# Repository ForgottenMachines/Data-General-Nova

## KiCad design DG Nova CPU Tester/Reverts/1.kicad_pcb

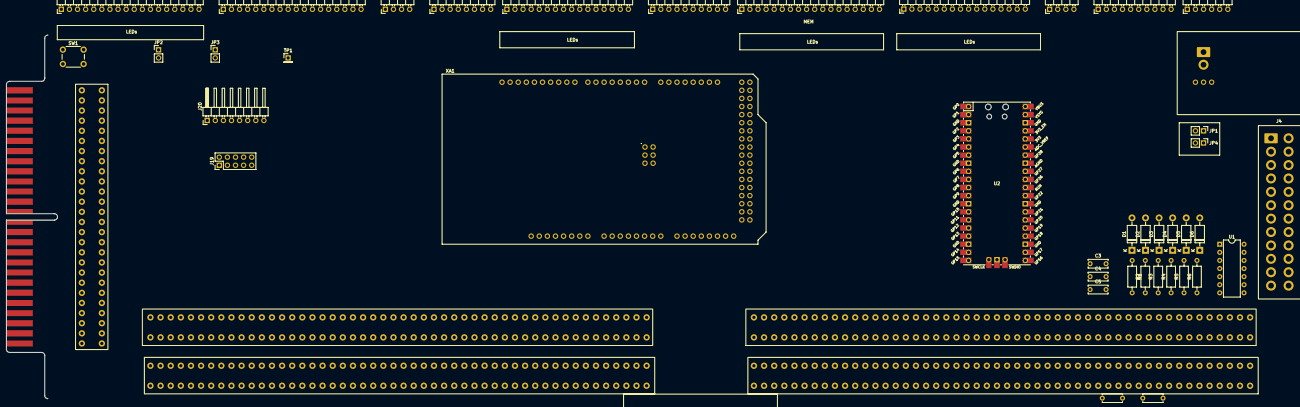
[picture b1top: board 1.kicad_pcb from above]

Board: 2 copper layers, 48 parts (0 on the bottom side), 153 nets, no tracks yet.

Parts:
C1, C2: CAP_Disc_Common_-_Entrex_Trapezoid; Disc Capacitor Common Entrex Trapezoid
C3, C4, C5: C; C_Disc_D6.0mm_W2.5mm_P5.00mm
D1, D2, D3, D4, D5, D6: 1N4004; D_DO-41_SOD81_P10.16mm_Horizontal
FPIMAGE1: MountingHole; nova frontpanel layout
J1: Front Panel Socket - Backside; DG NOVA Front Pannel Connector - Backside
J2, J3: DG NOVA Backplane Connector - Frontside
J4: ATX-24; Connector_2x12_P4.2mmx5.5mm (ATX Plug)
J5: Front Panel Card Edge; DG Nova Front Panel Card Edge
J6: MBO; PinHeader_1x16_P2.54mm_Horizontal
J7: MEM; PinHeader_1x18_P2.54mm_Horizontal
J8: Data Channel; PinHeader_1x16_P2.54mm_Horizontal
J9: Front Panel Controls; PinHeader_1x18_P2.54mm_Horizontal
J10: Programmed I/O; PinHeader_1x18_P2.54mm_Horizontal
J11: CPU Option Inputs; PinHeader_1x10_P2.54mm_Horizontal
J12: Data Channel; PinHeader_1x08_P2.54mm_Horizontal
J13: Program Interrupt; PinHeader_1x04_P2.54mm_Horizontal
J14: System Control; PinHeader_1x04_P2.54mm_Horizontal
J15, J16: Slot_02x50_Odd_Even; DG NOVA Backplane Connector - Backside
J17: CPU Option Outputs; PinHeader_1x06_P2.54mm_Horizontal
J18: MEM Control Outputs; PinHeader_1x10_P2.54mm_Horizontal
J19: Logic 8 CH; PinHeader_2x05_P2.54mm_Vertical
J20: Logic 8 CH; PinHeader_1x08_P2.54mm_Horizontal
JP1, JP4: Vipass Ammeter; PinHeader_1x02_P2.54mm_Vertical
JP2: Entrex ~{M CON DATA}; PinHeader_1x02_P2.54mm_Vertical
JP3: Entrex ~{M CON INST}; PinHeader_1x02_P2.54mm_Vertical
MES1: XK-001; XK-001_Volt-Amp_Meter - Backside
R1, R6: 1k; R_Axial_DIN0207_L6.3mm_D2.5mm_P10.16mm_Horizontal
R2, R5: 10k; R_Axial_DIN0207_L6.3mm_D2.5mm_P10.16mm_Horizontal
R3, R4: 4.7k; R_Axial_DIN0207_L6.3mm_D2.5mm_P10.16mm_Horizontal
SW1: SW_Push; SW_PUSH_6mm
TP1: Entrex Backplane S01B53 to S13B53; PinHeader_1x01_P2.54mm_Vertical
U1: 74HC14; DIP-14_W7.62mm
U2: Pico; RPi_Pico_SMD_TH
XA1: Arduino_Mega2560_Shield

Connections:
+3v3: J4.1 (+3.3V), J4.2 (+3.3V), J4.12 (+3.3V), J4.13 (+3.3V)
+5V: D1.1 (K), D2.2 (A), D3.1 (K), D4.2 (A), D5.1 (K), D6.2 (A), J2.3, J2.4, J2.97, J2.98, J3.3, J3.4, J3.97, J3.98, J4.4 (+5V), J4.6 (+5V), J4.21 (+5V), J4.22 (+5V), J4.23 (+5V), J5.27, J15.3, J15.4, J15.97 (Pin_69), J15.98, J16.3, J16.4, J16.97 (Pin_69), J16.98, MES1.1, MES1.3 (PWR), U1.14 (VCC), U2.39 (VSYS), XA1.5V1 (5V), XA1.5V3 (5V), XA1.5V4 (5V), XA1.VIN
+5V OK: J2.8, J14.3, U1.12
+12V Lamp: J1.33, J4.10 (+12V), J4.11 (+12V), J5.33
+VINH: J15.10, J16.84
-5V: J15.6, J16.81
CLK FLOP: J3.48, J17.1
CLR: J2.50, J10.14, J15.50
DATIA: J2.44, J10.7, J15.44
DATIB: J2.42, J10.8, J15.42
DATIC: J2.54, J10.9, J15.54
DATOA: J2.58, J10.10, J15.58
DATOB: J2.56, J10.11, J15.56
DATOC: J2.48, J10.12, J15.48
DCHI: J3.37, J12.6, J16.37
DCHO: J3.33, J12.7, J16.33
Entrex Backplane S01B53 to S13B53: J3.53, TP1.1
Entrex P10.19: J2.24, JP3.2 (B)
Entrex P10.30: J2.29, JP2.2 (B)
GND: C1.1, C2.1, C3.2, C4.2, C5.2, J1.1, J1.40, J2.1, J2.2, J2.33, J2.34, J2.99, J2.100, J3.1, J3.2, J3.50, J3.99, J3.100, J5.1, J5.40, J15.1, J15.2, J15.33, J15.34, J15.99, J15.100, J16.1, J16.2, J16.50, J16.89, J16.92, J16.99, J16.100, J19.10, JP1.2 (B), JP4.2 (B), MES1.5, SW1.1, U1.7 (GND), U2.3 (GND), U2.8 (GND), U2.13 (GND), U2.18 (GND), U2.23 (GND), U2.28 (GND), U2.33 (AGND), U2.38 (GND), U2.42 (GND), XA1.GND1 (GND), XA1.GND2 (GND), XA1.GND3 (GND), XA1.GND5 (GND), XA1.GND6 (GND)
GND After Meter: J4.3 (GND), J4.5 (GND), J4.7 (GND), J4.15 (GND), J4.17 (GND), J4.18 (GND), J4.19 (GND), J4.24 (GND), JP1.1 (A), JP4.1 (A), MES1.2, MES1.4
INH GND: J15.8, J15.14, J15.16, J15.20, J15.22, J15.26, J15.30, J15.31
INHIBIT: J3.30, J16.30, J18.9
INTA: J2.40, J13.4, J15.40
IO PLS: J2.74, J10.15, J15.74
IO RST: J2.70, J14.1, J15.70
LOAD IR: J2.73, J17.3
Logic1: J19.1, J20.1
Logic2: J19.2, J20.2
Logic3: J19.3, J20.3
Logic4: J19.4, J20.4
Logic5: J19.5, J20.5
Logic6: J19.6, J20.6
Logic7: J19.7, J20.7
Logic8: J19.8, J20.8
MB LOAD: J3.74, J16.74, J18.6
MEM OK: J2.9, J7.18, U1.10, XA1.D52
unnamed: C3.1, R1.2, R2.1, U1.5
unnamed: C4.1, R3.2, R4.1, U1.3
unnamed: C5.1, R5.2, R6.1, U1.1
unnamed: D1.2 (A), R1.1
unnamed: D2.1 (K), R2.2
unnamed: D3.2 (A), R3.1
unnamed: D4.1 (K), R4.2
unnamed: D5.2 (A), R5.1
unnamed: D6.1 (K), R6.2
unnamed: U1.6, U1.9
unnamed: U1.4, U1.11
unnamed: U1.2, U1.13
unnamed: SW1.2, XA1.RST1 (RESET)
OVFLO: J3.39, J12.8, J16.39
RESTART ENABLE: J1.19, J2.32, J5.19, J9.16, XA1.A7
STROBE: J3.20, J16.20, J18.8
STRT: J2.52, J10.13, J15.52
~CARRY: J1.49, J2.15, J5.49, J9.3, XA1.D32
~CON DATA: J1.46, J2.28, J5.46, J9.11, JP2.1 (A), XA1.D0 (D0_RX0)
~CON INST: J1.22, J2.22, J5.22, J9.10, JP3.1 (A), XA1.A4
~CON RQ: C2.2, J1.21, J2.27, J5.21, J9.9, XA1.A5
~CONT+ISTP+MSTP: J1.47, J2.25, J5.47, J9.12, XA1.D1 (D1_TX0)
~DATA0: J3.62, J8.1, J16.62
~DATA1: J3.65, J8.2, J16.65
~DATA2: J3.82, J8.3, J16.82
~DATA3: J3.73, J8.4, J16.73
~DATA4: J3.61, J8.5, J16.61
~DATA5: J3.57, J8.6, J16.57
~DATA6: J3.95, J8.7, J16.95
~DATA7: J3.55, J8.8, J16.55
~DATA8: J3.60, J8.9, J16.60
~DATA9: J3.63, J8.10, J16.63
~DATA10: J3.75, J8.11, J16.75
~DATA11: J3.58, J8.12, J16.58
~DATA12: J3.59, J8.13, J16.59
~DATA13: J3.64, J8.14, J16.64
~DATA14: J3.56, J8.15, J16.56
~DATA15: J3.66, J8.16, J16.66
~DCHA: J2.60, J12.3, J15.60
~DCHM0: J3.17, J12.4, J16.17
~DCHM1: J3.21, J12.5, J16.21
~DCHR: J3.35, J12.1, J16.35
~DEFER: J1.52, J2.12, J5.52, J9.5, XA1.D50
~DIV: J2.91, J11.2
~DRIVE IO: J3.88, J16.88, J18.1
~DS0: J2.72, J10.1, J15.72
~DS1: J2.68, J10.2, J15.68
~DS2: J2.66, J10.3, J15.66
~DS3: J2.46, J10.4, J15.46
~DS4: J2.62, J10.5, J15.62
~DS5: J2.64, J10.6, J15.64
~EXEC: J1.51, J2.11, J5.51, J9.6, XA1.D51
~EXT LOAD: J2.47, J3.49, J11.4
~FETCH: J1.50, J2.13, J2.49, J5.50, J9.4, XA1.D49
~FORCE LOAD IR: J2.85, J11.3
~INH TRANS: J3.45, J16.45, J18.10
~INTR: J3.29, J13.1, J16.29
~ION: J1.25, J2.16, J5.25, J9.2, XA1.D31
~ISTP: J1.24, J2.17, J5.24, J9.14, XA1.A2
~LOAD AC: J2.77, J17.2
~MA LOAD: J3.7, J16.7, J18.5
~MB CLEAR: J3.86, J16.86, J18.7
~MBO0: J3.79, J6.1, J16.79
~MBO1: J1.14, J3.77, J5.14, J6.2, J16.77, XA1.D15 (D15_RX3)
~MBO2: J1.15, J3.44, J5.15, J6.3, J16.44, XA1.D16 (D16_TX2)
~MBO3: J1.38, J3.43, J5.38, J6.4, J16.43, XA1.D17 (D17_RX2)
~MBO4: J1.16, J3.42, J5.16, J6.5, J16.42, XA1.D18 (D18_TX1)
~MBO5: J1.11, J3.32, J5.11, J6.6, J16.32, XA1.D19 (D19_RX1)
~MBO6: J1.35, J3.16, J5.35, J6.7, J16.16, XA1.D20 (D20_SDA)
~MBO7: J1.9, J3.14, J5.9, J6.8, J16.14, XA1.D21 (D21_SCL)
~MBO8: J1.18, J3.12, J5.18, J6.9, J16.12, XA1.D22
~MBO9: J1.8, J3.9, J5.8, J6.10, J16.9, XA1.D23
~MBO10: J1.44, J3.8, J5.44, J6.11, J16.8, XA1.D24
~MBO11: J1.6, J3.5, J5.6, J6.12, J16.5, XA1.D25
~MBO12: J1.30, J2.39, J5.30, J6.13, J15.39, XA1.D26
~MBO13: J1.4, J2.37, J5.4, J6.14, J15.37, XA1.D27
~MBO14: J1.12, J2.43, J5.12, J6.15, J15.43, XA1.D28
~MBO15: J1.28, J2.41, J5.28, J6.16, J15.41, XA1.D29
~MD SEL1: J2.87, J17.4
~MEM0: J1.39, J3.71, J5.39, J7.1, J16.71, XA1.D33
~MEM1: J1.41, J3.70, J5.41, J7.2, J16.70, XA1.D34
~MEM2: J1.13, J3.47, J5.13, J7.3, J16.47, XA1.D35
~MEM3: J1.43, J3.68, J5.43, J7.4, J16.68, XA1.D36
~MEM4: J1.37, J3.28, J5.37, J7.5, J16.28, XA1.D37
~MEM5: J1.36, J3.26, J5.36, J7.6, J16.26, XA1.D38
~MEM6: J1.10, J3.22, J5.10, J7.7, J16.22, XA1.D39
~MEM7: J1.42, J3.24, J5.42, J7.8, J16.24, XA1.D40
~MEM8: J1.34, J2.55, J5.34, J7.9, J15.55, XA1.D41
~MEM9: J1.7, J2.53, J5.7, J7.10, J15.53, XA1.D42
~MEM10: J1.32, J2.45, J5.32, J7.11, J15.45, XA1.D43
~MEM11: J1.31, J2.51, J5.31, J7.12, J15.51, XA1.D44
~MEM12: J1.5, J2.36, J5.5, J7.13, J15.36, XA1.D45
~MEM13: J1.29, J2.35, J5.29, J7.14, J15.35, XA1.D46
~MEM14: J1.3, J3.76, J5.3, J7.15, J16.76, XA1.D47
~MEM15: J1.2, J3.18, J5.2, J7.16, J16.18, XA1.D48
~MSKO: J2.38, J13.2, J15.38
~MSTP: J1.48, J2.20, J5.48, J9.13
~PL: C1.2, J1.23, J2.19, J5.23, J9.15, XA1.A3
~POWER FAIL: J2.5, J14.4, U1.8
~READ1: J3.87, J16.87, J18.3
~READ2: J3.90, J16.90, J18.4
~READ IO: J3.83, J16.83, J18.2
~RQENB: J3.41, J14.2, J16.41
~RST: J1.20, J2.30, J5.20, J9.17, XA1.A6
~RUN: J1.26, J2.14, J5.26, J9.1, XA1.D30
~SELB: J2.82, J10.16, J15.82
~SELD: J2.80, J10.17, J15.80
~SHIFT0: J3.94, J11.7
~SHIFT1: J3.96, J11.8
~SHIFT2: J3.93, J11.9
~SHIFT3: J3.91, J11.10
~SKIP: J3.69, J9.7
~STOP: J1.45, J2.31, J5.45, J9.8, XA1.D14 (D14_TX3)
~TEST: J2.92, J11.5
~WAS JSR: J2.89, J17.5
~WHOA: J3.6, J11.1

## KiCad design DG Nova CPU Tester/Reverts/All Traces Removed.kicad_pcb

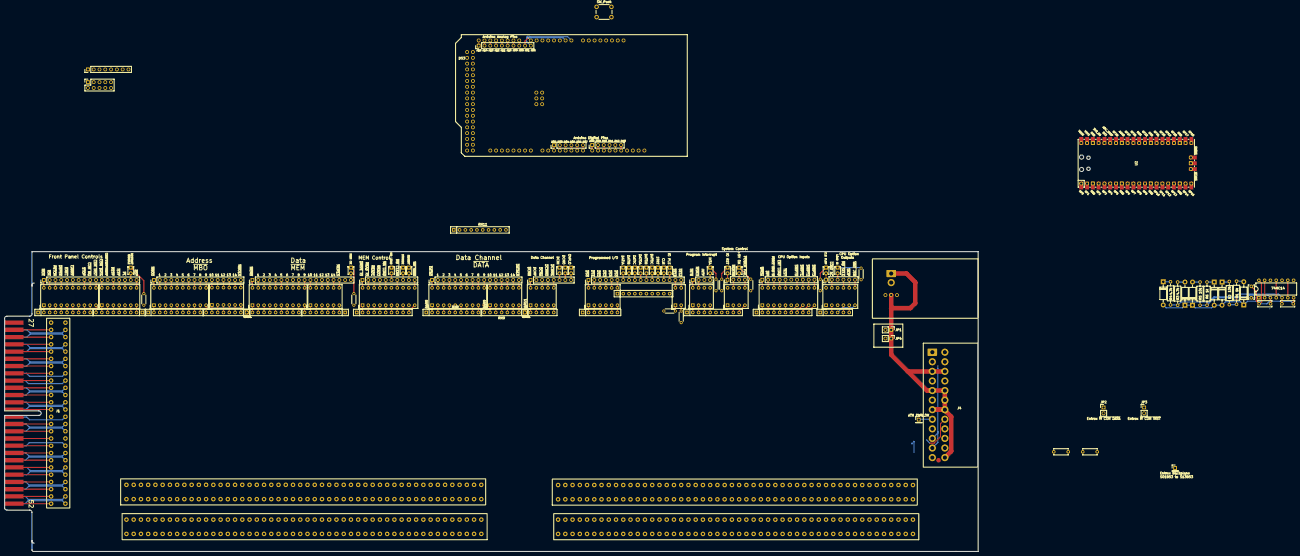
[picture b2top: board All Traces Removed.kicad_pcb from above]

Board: 2 copper layers, 426.8 x 131.4 mm, 115 parts (0 on the bottom side), 304 nets.

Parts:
BAR1, BAR3, BAR5, BAR7, BAR8, BAR15: LED Bar 10
BAR2: LED Bar 10; LED Bar 7
BAR4, BAR6, BAR9, BAR10, BAR16: LED Bar 10; LED Bar 6
BAR11: LED Bar 10; LED Bar 5
BAR12: LED Bar 2
BAR13, BAR14: LED Bar 4
C1, C2: CAP_Disc_Common_-_Entrex_Trapezoid; Disc Capacitor Common Entrex Trapezoid
C3, C4, C5: C; C_Disc_D6.0mm_W2.5mm_P5.00mm
D1, D2, D3, D4, D5, D6: 1N4004; D_DO-41_SOD81_P10.16mm_Horizontal
D7, D8, D9, D10, D11, D12, D13, D14, D15, D16, D17, D18, D19, D20, D21, D22, D23, D24, D25, D26, D27, D28: LED; LED_D1.8mm_W3.3mm_H2.4mm
FPIMAGE1: MountingHole; nova frontpanel layout
J1: Front Panel Socket - Backside; DG NOVA Front Pannel Connector - Backside
J2, J3: DG NOVA Backplane Connector - Frontside
J4: ATX-24; Connector_2x12_P4.2mmx5.5mm (ATX Plug)
J5: Front Panel Card Edge; DG Nova Front Panel Card Edge
J6: MBO; PinHeader_1x16_P2.54mm_Vertical
J7: MEM; PinHeader_1x18_P2.54mm_Vertical
J8: Data Channel; PinHeader_1x16_P2.54mm_Vertical
J9: Front Panel Controls; PinHeader_1x17_P2.54mm_Vertical
J10: Programmed I/O; PinHeader_1x17_P2.54mm_Vertical
J11: CPU Option Inputs; PinHeader_1x10_P2.54mm_Vertical
J12: Data Channel; PinHeader_1x08_P2.54mm_Vertical
J13: Program Interrupt; PinHeader_1x04_P2.54mm_Vertical
J14: System Control; PinHeader_1x04_P2.54mm_Vertical
J15, J16: Slot_02x50_Odd_Even; DG NOVA Backplane Connector - Backside
J17: CPU Option Outputs; PinHeader_1x06_P2.54mm_Vertical
J18: MEM Control Outputs; PinHeader_1x10_P2.54mm_Vertical
J19: Logic 8 CH; PinHeader_2x05_P2.54mm_Vertical - Backside
J20: Logic 8 CH; PinHeader_1x08_P2.54mm_Vertical
J21: Arduino Anolog Pins; PinHeader_1x10_P2.54mm_Vertical
J22, J23: Arduino Digital Pins; PinHeader_1x06_P2.54mm_Vertical
JP1, JP4: Vipass Ammeter; PinHeader_1x02_P2.54mm_Vertical
JP2: Entrex ~{M CON DATA}; PinHeader_1x02_P2.54mm_Vertical
JP3: Entrex ~{M CON INST}; PinHeader_1x02_P2.54mm_Vertical
MES1: XK-001; XK-001_Volt-Amp_Meter - Backside
R1, R6: 1k; R_Axial_DIN0207_L6.3mm_D2.5mm_P10.16mm_Horizontal
R2, R5: 10k; R_Axial_DIN0207_L6.3mm_D2.5mm_P10.16mm_Horizontal
R3, R4: 4.7k; R_Axial_DIN0207_L6.3mm_D2.5mm_P10.16mm_Horizontal
R7, R8, R9, R10, R11, R12, R13, R14, R15: R_US; R_Axial_DIN0204_L3.6mm_D1.6mm_P5.08mm_Horizontal
RN1, RN3, RN5, RN7, RN8, RN11, RN13, RN14, RN15: R_Network09_US; R_Array_SIP10
RN2: R_Network08_US; R_Array_SIP9
RN4, RN6, RN9: R_Network07_US; R_Array_SIP8
RN10, RN16: R_Network05_US; R_Array_SIP6
RN12: R_Network06_US; R_Array_SIP7
SW1: SW_Push; SW_PUSH_6mm
TP1: Entrex Backplane S01B53 to S13B53; PinHeader_1x01_P2.54mm_Vertical
TP2: ATX PWR_OK; PinHeader_1x01_P2.54mm_Vertical
U1: 74HC14; DIP-14_W7.62mm
U2: Pico; RPi_Pico_SMD_TH
XA1: Arduino_Mega2560_Shield

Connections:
+3v3: J4.1 (+3.3V), J4.2 (+3.3V), J4.12 (+3.3V), J4.13 (+3.3V)
+5V: D1.1 (K), D2.2 (A), D3.1 (K), D4.2 (A), D5.1 (K), D6.2 (A), J1.27, J2.3, J2.4, J2.97, J2.98, J3.3, J3.4, J3.97, J3.98, J4.4 (+5V), J4.6 (+5V), J4.21 (+5V), J4.22 (+5V), J4.23 (+5V), J5.27, J15.3, J15.4, J15.97 (Pin_69), J15.98, J16.3, J16.4, J16.97 (Pin_69), J16.98, MES1.1, MES1.3 (PWR), R9.1, R10.1, RN1.1 (common), RN2.1 (common), RN3.1 (common), RN4.1 (common), RN5.1 (common), RN6.1 (common), RN7.1 (common), RN8.1 (common), RN9.1 (common), RN10.1 (common), RN12.1 (common), RN13.1 (common), RN15.1 (common), RN16.1 (common), U1.14 (VCC), U2.39 (VSYS), XA1.5V1 (5V), XA1.5V3 (5V), XA1.5V4 (5V), XA1.VIN
+5V OK: D24.2 (A), J2.8, J14.3, U1.12
+12V Lamp: J1.33, J4.10 (+12V), J4.11 (+12V), J5.33
+VINH: J15.10, J16.84
-5V: J4.20 (-5v), J15.6, J16.81
CLK FLOP: D28.2 (A), J3.48, J17.1
CLR: D20.2 (A), J2.50, J10.14, J15.50
DATIA: D12.2 (A), J2.44, J10.7, J15.44
DATIB: D16.2 (A), J2.42, J10.8, J15.42
DATIC: D17.2 (A), J2.54, J10.9, J15.54
DATOA: D21.2 (A), J2.58, J10.10, J15.58
DATOB: D22.2 (A), J2.56, J10.11, J15.56
DATOC: D18.2 (A), J2.48, J10.12, J15.48
DCHI: D13.2 (A), J3.37, J12.6, J16.37
DCHO: D14.2 (A), J3.33, J12.7, J16.33
Entrex Backplane S01B53 to S13B53: J3.53, TP1.1
Entrex P10.19: J2.24, JP3.2 (B)
Entrex P10.30: J2.29, JP2.2 (B)
GND: C1.1, C2.1, C3.2, C4.2, C5.2, J1.1, J1.40, J2.1, J2.2, J2.33, J2.34, J2.99, J2.100, J3.1, J3.2, J3.50, J3.99, J3.100, J5.1, J5.40, J15.1, J15.2, J15.33, J15.34, J15.99, J15.100, J16.1, J16.2, J16.50, J16.89, J16.92, J16.99, J16.100, J19.10, JP1.2 (B), JP4.2 (B), MES1.5, R7.1, R8.1, R11.1, R12.1, R13.1, R14.1, R15.1, RN11.1 (common), RN14.1 (common), SW1.1, U1.7 (GND), U2.3 (GND), U2.8 (GND), U2.13 (GND), U2.18 (GND), U2.23 (GND), U2.28 (GND), U2.33 (AGND), U2.38 (GND), U2.42 (GND), XA1.GND1 (GND), XA1.GND2 (GND), XA1.GND3 (GND), XA1.GND5 (GND), XA1.GND6 (GND)
GND After Meter: J4.3 (GND), J4.5 (GND), J4.7 (GND), J4.15 (GND), J4.17 (GND), J4.18 (GND), J4.19 (GND), J4.24 (GND), JP1.1 (A), JP4.1 (A), MES1.2, MES1.4
INH GND: J15.8, J15.14, J15.16, J15.20, J15.22, J15.26, J15.30, J15.31
INHIBIT: D11.2 (A), J3.30, J16.30, J18.9
INTA: D25.2 (A), J2.40, J13.4, J15.40
IO PLS: D23.2 (A), J2.74, J10.15, J15.74
IO RST: D26.2 (A), J2.70, J14.1, J15.70
LOAD IR: D27.2 (A), J2.73, J17.3
Logic1: J19.1, J20.1
Logic2: J19.2, J20.2
Logic3: J19.3, J20.3
Logic4: J19.4, J20.4
Logic5: J19.5, J20.5
Logic6: J19.6, J20.6
Logic7: J19.7, J20.7
Logic8: J19.8, J20.8
MB LOAD: D9.2 (A), J3.74, J16.74, J18.6
MEM OK: D8.2 (A), J2.9, J7.18, U1.10, XA1.D52
unnamed: BAR12.1, R10.2
unnamed: BAR12.2, R9.2
unnamed: C3.1, R1.2, R2.1, U1.5
unnamed: C4.1, R3.2, R4.1, U1.3
unnamed: C5.1, R5.2, R6.1, U1.1
unnamed: D1.2 (A), R1.1
unnamed: D2.1 (K), R2.2
unnamed: D3.2 (A), R3.1
unnamed: D4.1 (K), R4.2
unnamed: D5.2 (A), R5.1
unnamed: D6.1 (K), R6.2
unnamed: D7.1 (K), R7.2
unnamed: D8.1 (K), R8.2
unnamed: D9.1 (K), RN11.2 (R1)
unnamed: D10.1 (K), RN11.3 (R2)
unnamed: D11.1 (K), RN11.4 (R3)
unnamed: D12.1 (K), RN14.2 (R1)
unnamed: D13.1 (K), RN11.7 (R6)
unnamed: D14.1 (K), RN11.8 (R7)
unnamed: D15.1 (K), RN11.9 (R8)
unnamed: D16.1 (K), RN14.3 (R2)
unnamed: D17.1 (K), RN14.4 (R3)
unnamed: D18.1 (K), RN14.7 (R6)
unnamed: D19.1 (K), RN14.8 (R7)
unnamed: D20.1 (K), RN14.9 (R8)
unnamed: D21.1 (K), RN14.5 (R4)
unnamed: D22.1 (K), RN14.6 (R5)
unnamed: D23.1 (K), RN14.10 (R9)
unnamed: D24.1 (K), R14.2
unnamed: D25.1 (K), R11.2
unnamed: D26.1 (K), R12.2
unnamed: D27.1 (K), R13.2
unnamed: D28.1 (K), R15.2
unnamed: J21.1, XA1.A15
unnamed: J21.2, XA1.A14
unnamed: J21.3, XA1.A13
unnamed: J21.4, XA1.A12
unnamed: J21.5, XA1.A11
unnamed: J21.6, XA1.A10
unnamed: J21.7, XA1.A9
unnamed: J21.8, XA1.A8
unnamed: J21.9, XA1.A1
unnamed: J21.10, XA1.A0
unnamed: J22.1, XA1.D2 (D2_INT0)
unnamed: J22.2, XA1.D3 (D3_INT1)
unnamed: J22.3, XA1.D4
unnamed: J22.4, XA1.D5
unnamed: J22.5, XA1.D6
unnamed: J22.6, XA1.D7
unnamed: J23.1, XA1.D8
unnamed: J23.2, XA1.D9
unnamed: J23.3, XA1.D10
unnamed: J23.4, XA1.D11
unnamed: J23.5, XA1.D12
unnamed: J23.6, XA1.D13
unnamed: BAR1.1, RN1.2 (R1)
unnamed: BAR1.2, RN1.3 (R2)
unnamed: BAR1.3, RN1.4 (R3)
unnamed: BAR1.4, RN1.5 (R4)
unnamed: BAR1.5, RN1.6 (R5)
unnamed: BAR1.6, RN1.7 (R6)
unnamed: BAR1.7, RN1.8 (R7)
unnamed: BAR1.8, RN1.9 (R8)
unnamed: BAR1.9, RN1.10 (R9)
unnamed: BAR2.7, RN2.2 (R1)
unnamed: BAR2.6, RN2.3 (R2)
unnamed: BAR2.5, RN2.4 (R3)
unnamed: BAR2.4, RN2.5 (R4)
unnamed: BAR2.3, RN2.6 (R5)
unnamed: BAR2.2, RN2.7 (R6)
unnamed: BAR2.1, RN2.8 (R7)
unnamed: BAR1.10, RN2.9 (R8)
unnamed: BAR3.1, RN3.2 (R1)
unnamed: BAR3.2, RN3.3 (R2)
unnamed: BAR3.3, RN3.4 (R3)
unnamed: BAR3.4, RN3.5 (R4)
unnamed: BAR3.5, RN3.6 (R5)
unnamed: BAR3.6, RN3.7 (R6)
unnamed: BAR3.7, RN3.8 (R7)
unnamed: BAR3.8, RN3.9 (R8)
unnamed: BAR3.9, RN3.10 (R9)
unnamed: BAR4.6, RN4.2 (R1)
unnamed: BAR4.5, RN4.3 (R2)
unnamed: BAR4.4, RN4.4 (R3)
unnamed: BAR4.3, RN4.5 (R4)
unnamed: BAR4.2, RN4.6 (R5)
unnamed: BAR4.1, RN4.7 (R6)
unnamed: BAR3.10, RN4.8 (R7)
unnamed: BAR5.1, RN5.2 (R1)
unnamed: BAR5.2, RN5.3 (R2)
unnamed: BAR5.3, RN5.4 (R3)
unnamed: BAR5.4, RN5.5 (R4)
unnamed: BAR5.5, RN5.6 (R5)
unnamed: BAR5.6, RN5.7 (R6)
unnamed: BAR5.7, RN5.8 (R7)
unnamed: BAR5.8, RN5.9 (R8)
unnamed: BAR5.9, RN5.10 (R9)
unnamed: BAR6.6, RN6.2 (R1)
unnamed: BAR6.5, RN6.3 (R2)
unnamed: BAR6.4, RN6.4 (R3)
unnamed: BAR6.3, RN6.5 (R4)
unnamed: BAR6.2, RN6.6 (R5)
unnamed: BAR6.1, RN6.7 (R6)
unnamed: BAR5.10, RN6.8 (R7)
unnamed: BAR7.1, RN7.2 (R1)
unnamed: BAR7.2, RN7.3 (R2)
unnamed: BAR7.3, RN7.4 (R3)
unnamed: BAR7.4, RN7.5 (R4)
unnamed: BAR7.5, RN7.6 (R5)
unnamed: BAR7.6, RN7.7 (R6)
unnamed: BAR7.7, RN7.8 (R7)
unnamed: BAR7.8, RN7.9 (R8)
unnamed: BAR7.10, RN7.10 (R9)
unnamed: BAR8.1, RN8.2 (R1)
unnamed: BAR8.2, RN8.3 (R2)
unnamed: BAR8.3, RN8.4 (R3)
unnamed: BAR8.4, RN8.5 (R4)
unnamed: BAR8.5, RN8.6 (R5)
unnamed: BAR8.6, RN8.7 (R6)
unnamed: BAR8.7, RN8.8 (R7)
unnamed: BAR8.8, RN8.9 (R8)
unnamed: BAR8.9, RN8.10 (R9)
unnamed: BAR9.6, RN9.2 (R1)
unnamed: BAR9.5, RN9.3 (R2)
unnamed: BAR9.4, RN9.4 (R3)
unnamed: BAR9.3, RN9.5 (R4)
unnamed: BAR9.2, RN9.6 (R5)
unnamed: BAR9.1, RN9.7 (R6)
unnamed: BAR8.10, RN9.8 (R7)
unnamed: BAR11.1, RN10.2 (R1)
unnamed: BAR11.2, RN10.3 (R2)
unnamed: BAR11.3, RN10.4 (R3)
unnamed: BAR11.4, RN10.5 (R4)
unnamed: BAR11.5, RN10.6 (R5)
unnamed: BAR10.1, RN12.2 (R1)
unnamed: BAR10.2, RN12.3 (R2)
unnamed: BAR10.3, RN12.4 (R3)
unnamed: BAR10.4, RN12.5 (R4)
unnamed: BAR10.5, RN12.6 (R5)
unnamed: BAR10.6, RN12.7 (R6)
unnamed: BAR13.1, RN13.2 (R1)
unnamed: BAR13.2, RN13.3 (R2)
unnamed: BAR13.3, RN13.4 (R3)
unnamed: BAR13.4, RN13.5 (R4)
unnamed: BAR14.2, RN13.9 (R8)
unnamed: BAR14.4, RN13.10 (R9)
unnamed: BAR15.1, RN15.2 (R1)
unnamed: BAR15.2, RN15.3 (R2)
unnamed: BAR15.3, RN15.4 (R3)
unnamed: BAR15.4, RN15.5 (R4)
unnamed: BAR15.5, RN15.6 (R5)
unnamed: BAR15.7, RN15.7 (R6)
unnamed: BAR15.8, RN15.8 (R7)
unnamed: BAR15.9, RN15.9 (R8)
unnamed: BAR15.10, RN15.10 (R9)
unnamed: BAR16.2, RN16.3 (R2)
unnamed: BAR16.6, RN16.4 (R3)
unnamed: BAR16.4, RN16.5 (R4)
unnamed: BAR16.5, RN16.6 (R5)
unnamed: U1.6, U1.9
unnamed: U1.4, U1.11
unnamed: U1.2, U1.13
unnamed: SW1.2, XA1.RST1 (RESET)
OVFLO: D15.2 (A), J3.39, J12.8, J16.39
PWR_OK: J4.8 (PWR_OK), TP2.1
RESTART ENABLE: D7.2 (A), J1.19, J2.32, J5.19, J9.16, XA1.A7
STROBE: D10.2 (A), J3.20, J16.20, J18.8
STRT: D19.2 (A), J2.52, J10.13, J15.52
~CARRY: BAR1.15 (K), J1.49, J2.15, J5.49, J9.6, XA1.D32
~CON DATA: BAR2.20 (K), J1.46, J2.28, J5.46, J9.11, JP2.1 (A), XA1.D0 (D0_RX0)
~CON INST: BAR1.11 (K), J1.22, J2.22, J5.22, J9.10, JP3.1 (A), XA1.A4
~CON RQ: BAR1.12 (K), C2.2, J1.21, J2.27, J5.21, J9.9, XA1.A5
~CONT+ISTP+MSTP: BAR2.19 (K), J1.47, J2.25, J5.47, J9.12, XA1.D1 (D1_TX0)
~DATA0: BAR8.20 (K), J3.62, J8.1, J16.62
~DATA1: BAR8.19 (K), J3.65, J8.2, J16.65
~DATA2: BAR8.18 (K), J3.82, J8.3, J16.82
~DATA3: BAR8.17 (K), J3.73, J8.4, J16.73
~DATA4: BAR8.16 (K), J3.61, J8.5, J16.61
~DATA5: BAR8.15 (K), J3.57, J8.6, J16.57
~DATA6: BAR8.14 (K), J3.95, J8.7, J16.95
~DATA7: BAR8.13 (K), J3.55, J8.8, J16.55
~DATA8: BAR8.12 (K), J3.60, J8.9, J16.60
~DATA9: BAR8.11 (K), J3.63, J8.10, J16.63
~DATA10: BAR9.20 (K), J3.75, J8.11, J16.75
~DATA11: BAR9.19 (K), J3.58, J8.12, J16.58
~DATA12: BAR9.18 (K), J3.59, J8.13, J16.59
~DATA13: BAR9.17 (K), J3.64, J8.14, J16.64
~DATA14: BAR9.16 (K), J3.56, J8.15, J16.56
~DATA15: BAR9.15 (K), J3.66, J8.16, J16.66
~DCHA: BAR11.18 (K), J2.60, J12.3, J15.60
~DCHM0: BAR11.17 (K), J3.17, J12.4, J16.17
~DCHM1: BAR11.16 (K), J3.21, J12.5, J16.21
~DCHR: BAR11.20 (K), J3.35, J12.1, J16.35
~DEFER: BAR1.17 (K), J1.52, J2.12, J5.52, J9.4, XA1.D50
~DIV: BAR15.19 (K), J2.91, J11.2
~DRIVE IO: BAR7.20 (K), J3.88, J16.88, J18.1
~DS0: BAR10.20 (K), J2.72, J10.1, J15.72
~DS1: BAR10.19 (K), J2.68, J10.2, J15.68
~DS2: BAR10.18 (K), J2.66, J10.3, J15.66
~DS3: BAR10.17 (K), J2.46, J10.4, J15.46
~DS4: BAR10.16 (K), J2.62, J10.5, J15.62
~DS5: BAR10.15 (K), J2.64, J10.6, J15.64
~EXEC: BAR1.16 (K), J1.51, J2.11, J5.51, J9.5, XA1.D51
~EXT LOAD: BAR15.17 (K), J2.47, J3.49, J11.4
~FETCH: BAR1.18 (K), J1.50, J2.13, J2.49, J5.50, J9.3, XA1.D49
~FORCE LOAD IR: BAR15.18 (K), J2.85, J11.3
~INH TRANS: BAR7.11 (K), J3.45, J16.45, J18.10
~INTR: BAR13.20 (K), J3.29, J13.1, J16.29
~ION: BAR1.19 (K), J1.25, J2.16, J5.25, J9.2, XA1.D31
~ISTP: BAR2.17 (K), J1.24, J2.17, J5.24, J9.14, XA1.A2
~LOAD AC: BAR16.19 (K), J2.77, J17.2
~MA LOAD: BAR7.16 (K), J3.7, J16.7, J18.5
~MB CLEAR: BAR7.14 (K), J3.86, J16.86, J18.7
~MBO0: BAR3.20 (K), J3.79, J6.1, J16.79
~MBO1: BAR3.19 (K), J1.14, J3.77, J5.14, J6.2, J16.77, XA1.D15 (D15_RX3)
~MBO2: BAR3.18 (K), J1.15, J3.44, J5.15, J6.3, J16.44, XA1.D16 (D16_TX2)
~MBO3: BAR3.17 (K), J1.38, J3.43, J5.38, J6.4, J16.43, XA1.D17 (D17_RX2)
~MBO4: BAR3.16 (K), J1.16, J3.42, J5.16, J6.5, J16.42, XA1.D18 (D18_TX1)
~MBO5: BAR3.15 (K), J1.11, J3.32, J5.11, J6.6, J16.32, XA1.D19 (D19_RX1)
~MBO6: BAR3.14 (K), J1.35, J3.16, J5.35, J6.7, J16.16, XA1.D20 (D20_SDA)
~MBO7: BAR3.13 (K), J1.9, J3.14, J5.9, J6.8, J16.14, XA1.D21 (D21_SCL)
~MBO8: BAR3.12 (K), J1.18, J3.12, J5.18, J6.9, J16.12, XA1.D22
~MBO9: BAR3.11 (K), J1.8, J3.9, J5.8, J6.10, J16.9, XA1.D23
~MBO10: BAR4.20 (K), J1.44, J3.8, J5.44, J6.11, J16.8, XA1.D24
~MBO11: BAR4.19 (K), J1.6, J3.5, J5.6, J6.12, J16.5, XA1.D25
~MBO12: BAR4.18 (K), J1.30, J2.39, J5.30, J6.13, J15.39, XA1.D26
~MBO13: BAR4.17 (K), J1.4, J2.37, J5.4, J6.14, J15.37, XA1.D27
~MBO14: BAR4.16 (K), J1.12, J2.43, J5.12, J6.15, J15.43, XA1.D28
~MBO15: BAR4.15 (K), J1.28, J2.41, J5.28, J6.16, J15.41, XA1.D29
~MD SEL1: BAR16.17 (K), J2.87, J17.4
~MEM0: BAR5.20 (K), J1.39, J3.71, J5.39, J7.1, J16.71, XA1.D33
~MEM1: BAR5.19 (K), J1.41, J3.70, J5.41, J7.2, J16.70, XA1.D34
~MEM2: BAR5.18 (K), J1.13, J3.47, J5.13, J7.3, J16.47, XA1.D35
~MEM3: BAR5.17 (K), J1.43, J3.68, J5.43, J7.4, J16.68, XA1.D36
~MEM4: BAR5.16 (K), J1.37, J3.28, J5.37, J7.5, J16.28, XA1.D37
~MEM5: BAR5.15 (K), J1.36, J3.26, J5.36, J7.6, J16.26, XA1.D38
~MEM6: BAR5.14 (K), J1.10, J3.22, J5.10, J7.7, J16.22, XA1.D39
~MEM7: BAR5.13 (K), J1.42, J3.24, J5.42, J7.8, J16.24, XA1.D40
~MEM8: BAR5.12 (K), J1.34, J2.55, J5.34, J7.9, J15.55, XA1.D41
~MEM9: BAR5.11 (K), J1.7, J2.53, J5.7, J7.10, J15.53, XA1.D42
~MEM10: BAR6.20 (K), J1.32, J2.45, J5.32, J7.11, J15.45, XA1.D43
~MEM11: BAR6.19 (K), J1.31, J2.51, J5.31, J7.12, J15.51, XA1.D44
~MEM12: BAR6.18 (K), J1.5, J2.36, J5.5, J7.13, J15.36, XA1.D45
~MEM13: BAR6.17 (K), J1.29, J2.35, J5.29, J7.14, J15.35, XA1.D46
~MEM14: BAR6.16 (K), J1.3, J3.76, J5.3, J7.15, J16.76, XA1.D47
~MEM15: BAR6.15 (K), J1.2, J3.18, J5.2, J7.16, J16.18, XA1.D48
~MSKO: BAR13.19 (K), J2.38, J13.2, J15.38
~MSTP: BAR2.18 (K), J1.48, J2.20, J5.48, J9.13
~PL: BAR2.16 (K), C1.2, J1.23, J2.19, J5.23, J9.15, XA1.A3
~POWER FAIL: BAR14.17 (K), J2.5, J14.4, U1.8
~READ1: BAR7.18 (K), J3.87, J16.87, J18.3
~READ2: BAR7.17 (K), J3.90, J16.90, J18.4
~READ IO: BAR7.19 (K), J3.83, J16.83, J18.2
~RQENB: BAR14.19 (K), J3.41, J14.2, J16.41
~RST: BAR2.14 (K), J1.20, J2.30, J5.20, J9.17, XA1.A6
~RUN: BAR1.20 (K), J1.26, J2.14, J5.26, J9.1, XA1.D30
~SELB: BAR12.20 (K), J2.82, J10.16, J15.82
~SELD: BAR12.19 (K), J2.80, J10.17, J15.80
~SHIFT0: BAR15.14 (K), J3.94, J11.7
~SHIFT1: BAR15.13 (K), J3.96, J11.8
~SHIFT2: BAR15.12 (K), J3.93, J11.9
~SHIFT3: BAR15.11 (K), J3.91, J11.10
~SKIP: BAR16.16 (K), J3.69, J17.5
~STOP: BAR1.13 (K), J1.45, J2.31, J5.45, J9.8, XA1.D14 (D14_TX3)
~TEST: BAR15.16 (K), J2.92, J11.5
~WAS JSR: BAR16.15 (K), J2.89, J17.6
~WHOA: BAR15.20 (K), J3.6, J11.1
